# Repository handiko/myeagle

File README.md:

# myeagle
Collection of my eagle

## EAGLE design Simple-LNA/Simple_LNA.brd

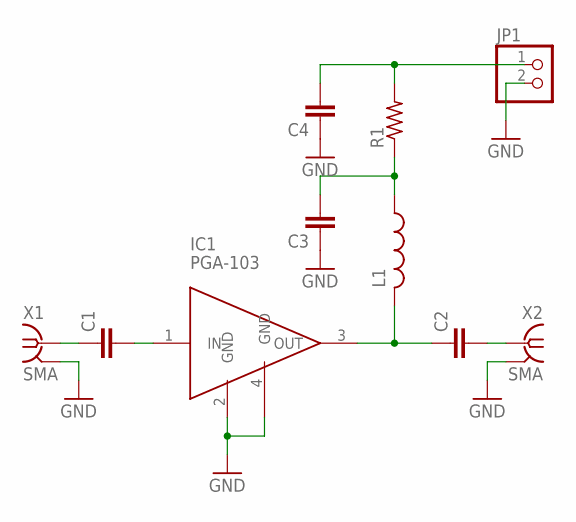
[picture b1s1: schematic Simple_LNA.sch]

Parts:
C1, C2, C3, C4: C-EUC0805; C0805
IC1: PGA-103; SOT89
JP1: PINHD-1X2; 1X02
L1: L-USL3216C; L3216C
R1: R-US_R0805; R0805
X1, X2: SMA; J502-ND-142-0701-801/806

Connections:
GND: C3.1, C4.1, IC1.2 (GND), IC1.4 (GND), JP1.2, X1.G@1 (2), X1.G@2 (2), X1.G@3 (2), X1.G@4 (2), X2.G@1 (2), X2.G@2 (2), X2.G@3 (2), X2.G@4 (2)
unnamed: C1.1, X1.1
unnamed: C1.2, IC1.1 (IN)
unnamed: C2.2, X2.1
unnamed: C2.1, IC1.3 (OUT), L1.2
unnamed: C4.2, JP1.1, R1.2
unnamed: C3.2, L1.1, R1.1

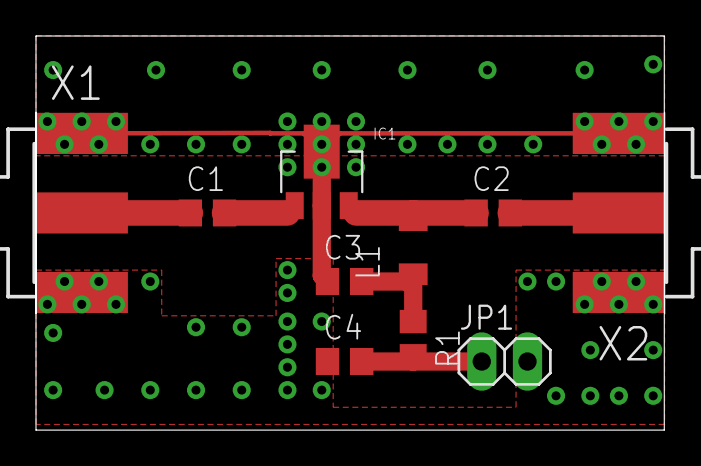
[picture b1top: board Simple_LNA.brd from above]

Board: 2 copper layers, 34.9 x 21.9 mm, 10 parts (0 on the bottom side), 7 nets.

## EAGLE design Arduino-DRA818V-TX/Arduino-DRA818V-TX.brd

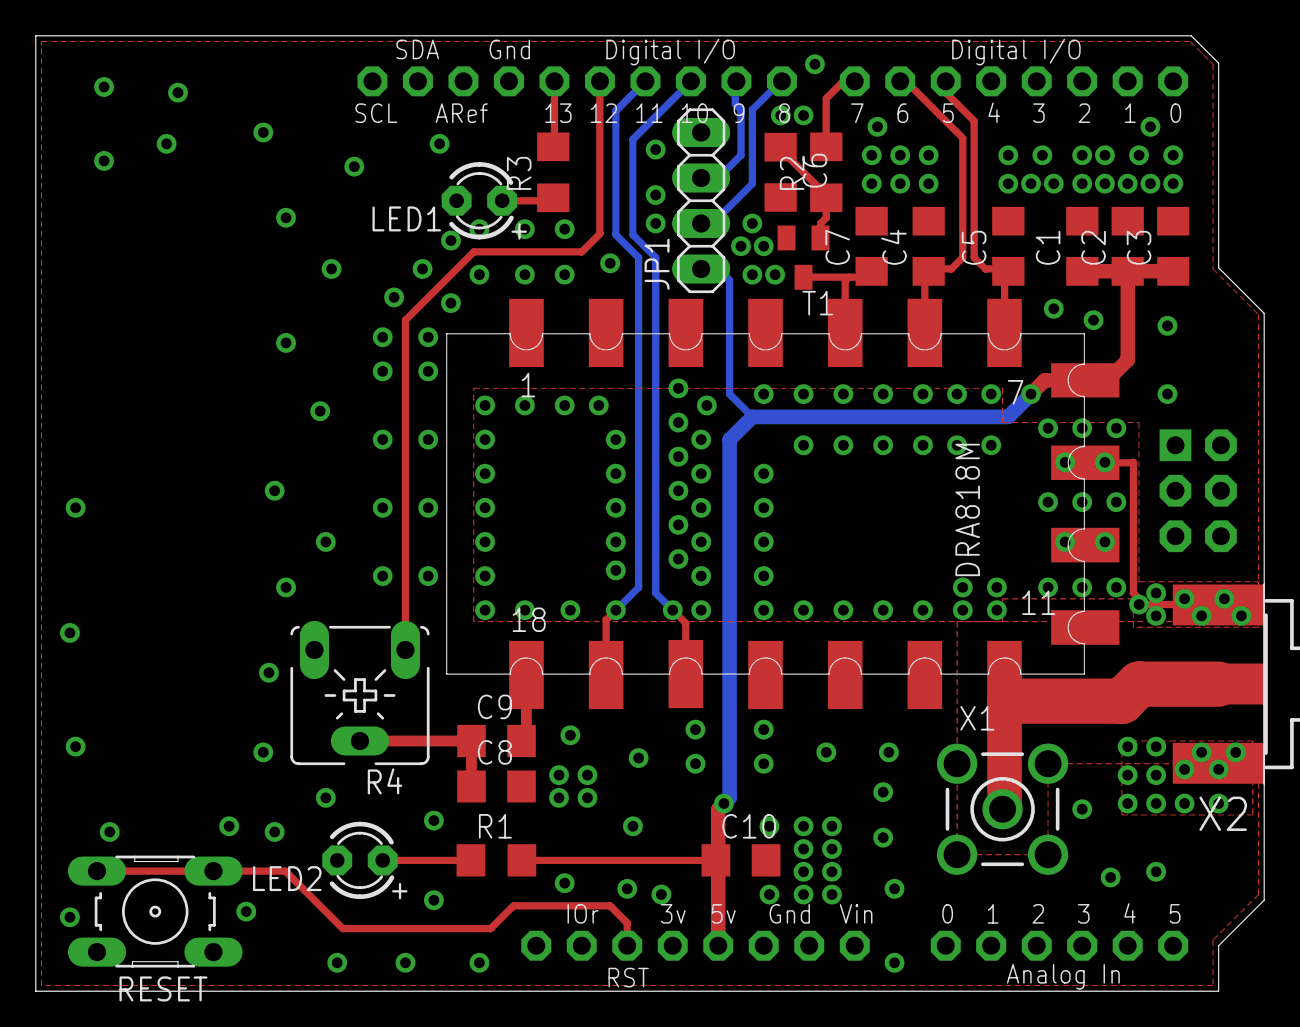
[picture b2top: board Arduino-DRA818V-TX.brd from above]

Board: 2 copper layers, 68.6 x 53.3 mm, 23 parts (0 on the bottom side), 19 nets.

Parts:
C1, C10: 1n; C1206
C2: 10n; C1206
C3, C9: 1u; C1206
C4, C5, C6, C7, C8: 100n; C1206
DRA818V: DRA818A
JP1: 1X04
LED1, LED2: LED3MM
M1: ARDUINO_R3_ICSP; ARDUINOR3_ICSP
R1, R3: 560; R1206
R2: 1k; R1206
R4: 10k; CA6V
RESET: Reset; B3F-10XX
T1: SOT23-BEC
X1: SMA; LTI-SASF54GT
X2: SMA; J502-ND-142-0701-801/806

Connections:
+5V: C1.1, C2.1, C3.1, C10.1, DRA818V.8, JP1.1, M1.5V, R1.2
AF_NORM: C9.2, DRA818V.18
AF_OUT: M1.D12, R4.A
GND: C1.2, C2.2, C3.2, C4.2, C5.2, C6.2, C7.2, C8.2, C10.2, DRA818V.9, DRA818V.10, JP1.4, LED1.K, LED2.K, M1.GND, M1.GND@1, M1.GND@2, M1.GND@3, R4.E, RESET.1, RESET.2, T1.E, X1.2, X1.3, X1.4, X1.5, X2.G@1, X2.G@2, X2.G@3, X2.G@4
LED_BUILTIN: M1.D13, R3.2
unnamed: DRA818V.12, X1.1, X2.1
unnamed: C6.1, R2.1, T1.B
unnamed: LED1.A, R3.1
unnamed: C8.1, C9.1, R4.S
unnamed: LED2.A, R1.1
PD: C4.1, DRA818V.6, M1.D6
POW: C5.1, DRA818V.7, M1.D5
PTT: M1.D7, R2.2
PTT_SW: C7.1, DRA818V.5, T1.C
RESET: M1.RESET, RESET.3, RESET.4
RXD_DRJ: DRA818V.16, M1.D10
RXD_GPS: JP1.2, M1.D8
TXD_DRJ: DRA818V.17, M1.D11
TXD_GPS: JP1.3, M1.D9

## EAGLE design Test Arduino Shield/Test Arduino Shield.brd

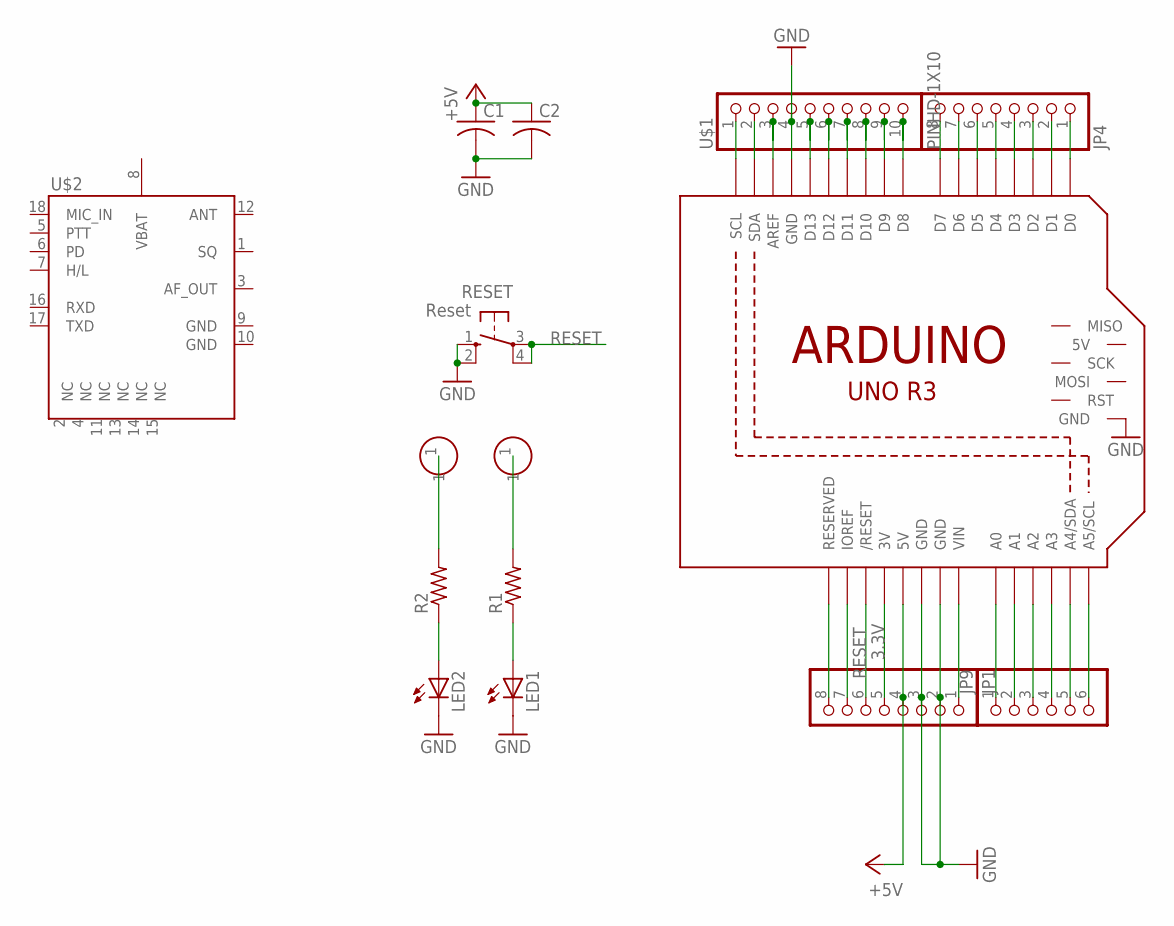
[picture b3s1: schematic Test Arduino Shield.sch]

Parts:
C1, C2: C-US025-025X050; C025-025X050
JP1, JP4: PINHD-1X8BIG; 1X08-BIG
JP9: PINHD-1X6B; 1X06-BIG
LED1, LED2: LED3MM
M1: ARDUINO_R3_ICSP; ARDUINOR3_ICSP
R1, R2: R-US_0207/5V; 0207/5V
RESET: Reset; B3F-10XX
U$1: PINHD-1X10; 1X10-BIG
U$2: DRA818A
U$4, U$7: PERFHOLE

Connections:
3.3V: JP1.5, M1.3V
+5V: C1.1, C2.1, JP1.4, M1.5V
GND: C1.2, C2.2, JP1.2, JP1.3, LED1.K (C), LED2.K (C), M1.GND, M1.GND@1 (GND), M1.GND@2 (GND), M1.GND@3 (GND), RESET.1 (S), RESET.2 (S1), U$1.4
unnamed: M1.AREF, U$1.3
unnamed: JP1.8, M1.RESERVED
unnamed: M1.D13, U$1.5
unnamed: LED1.A, R1.1
unnamed: JP1.7, M1.IOREF
unnamed: R1.2, U$7.1
unnamed: R2.2, U$4.1
unnamed: LED2.A, R2.1
unnamed: M1.D12, U$1.6
unnamed: M1.D11, U$1.7
unnamed: M1.D10, U$1.8
unnamed: M1.D9, U$1.9
unnamed: M1.D8, U$1.10
unnamed: JP9.1, M1.A0
unnamed: JP9.2, M1.A1
unnamed: JP9.3, M1.A2
unnamed: JP9.4, M1.A3
unnamed: JP9.5, M1.A4 (A4/SDA)
unnamed: JP9.6, M1.A5 (A5/SCL)
unnamed: JP4.1, M1.D0
unnamed: JP4.2, M1.D1
unnamed: JP4.3, M1.D2
unnamed: JP4.4, M1.D3
unnamed: JP4.5, M1.D4
unnamed: JP4.6, M1.D5
unnamed: JP4.7, M1.D6
unnamed: JP4.8, M1.D7
unnamed: JP1.1, M1.VIN
unnamed: M1.SCL, U$1.1
unnamed: M1.SDA, U$1.2
RESET: JP1.6, M1.RESET (/RESET), RESET.3, RESET.4 (P1)

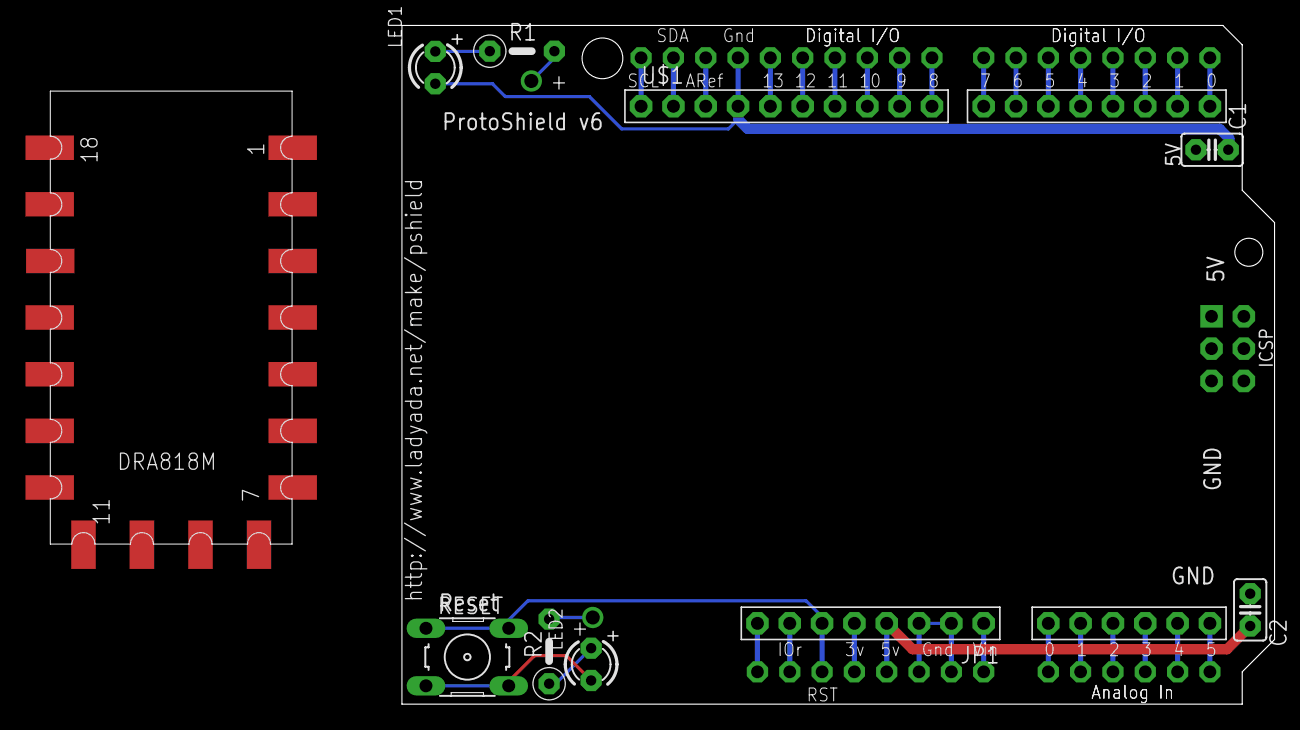
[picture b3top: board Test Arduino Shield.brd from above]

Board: 2 copper layers, 68.6 x 53.3 mm, 16 parts (1 on the bottom side), 34 nets.

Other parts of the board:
U$36: ADAFRUIT_9MM

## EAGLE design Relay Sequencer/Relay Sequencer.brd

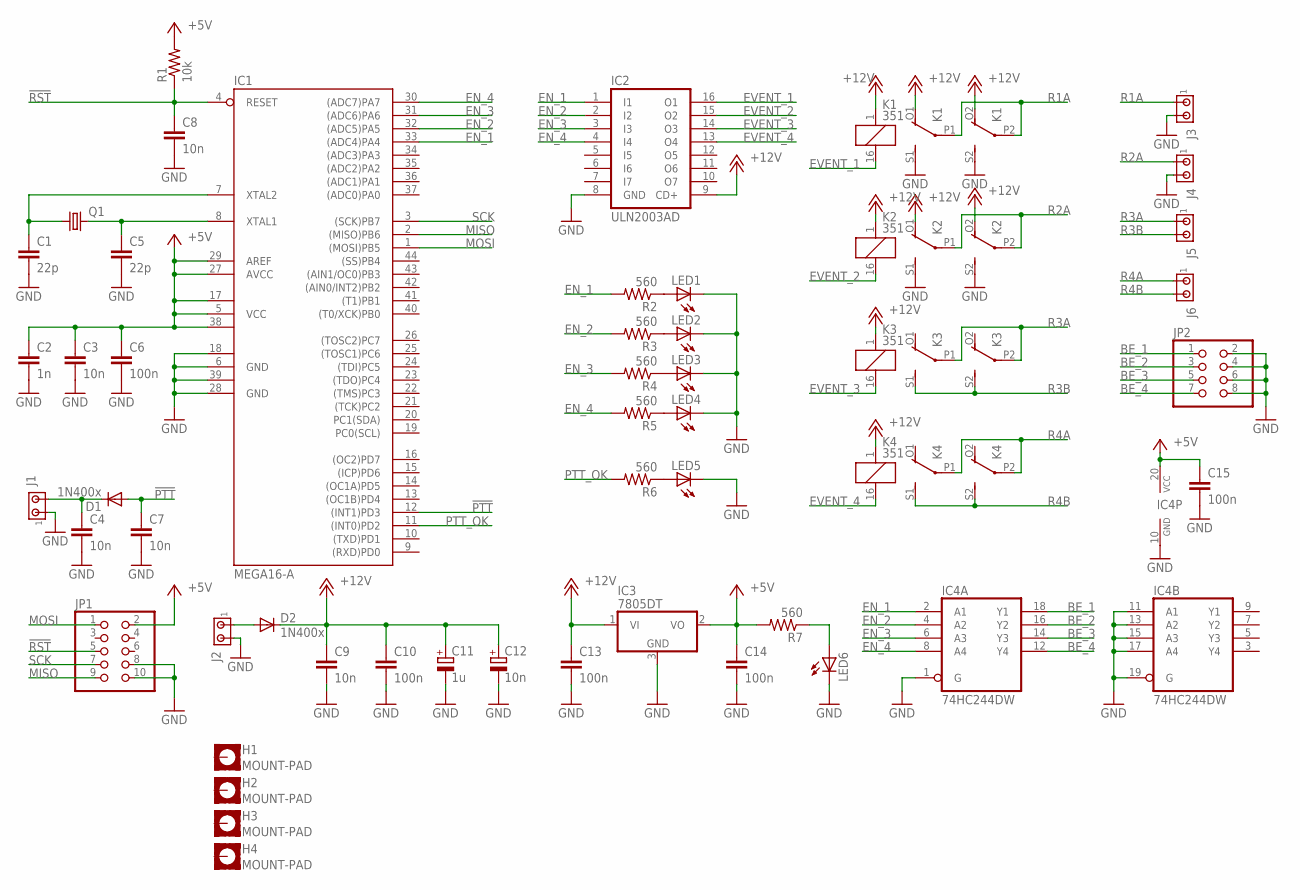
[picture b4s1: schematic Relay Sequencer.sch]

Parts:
C1, C5: 22p; C1206
C2: 1n; C1206
C3, C4, C7, C8, C9: 10n; C1206
C6, C10, C13, C14, C15: 100n; C1206
C11: 1u; E5-8,5
C12: 10n; E5-13
D1, D2: 1N400x; DO35-10
H1, H2, H3, H4: MOUNT-PAD; 2,8-PAD-SQUARE
IC1: MEGA16-A; TQFP44
IC2: ULN2003AD; SO16
IC3: 7805DT; TO252
IC4: 74HC244DW; SO20W
J1, J2, J3, J4, J5, J6: MTA02-156; 1X2MTA
JP1: PINHD-2X5; 2X05
JP2: PINHD-2X4; 2X04
K1, K2, K3, K4: 351
LED1, LED2, LED3, LED4, LED5, LED6: LED3MM
Q1: CRYSTALHC49S; HC49/S
R1: 10k; M1206
R2, R3, R4, R5, R6, R7: 560; M1206

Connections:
!PTT: C7.1, D1.A, IC1.12 ((INT1)PD3)
!RST: C8.1, IC1.4 (RESET), JP1.5, R1.1
+5V: C2.1, C3.1, C6.1, C14.1, C15.1, IC1.5 (VCC), IC1.17 (VCC1), IC1.27 (AVCC), IC1.29 (AREF), IC1.38 (VCC2), IC3.2 (VO), IC4.20 (VCC), JP1.2, R1.2, R7.2
+12V: C9.1, C10.1, C11.+, C12.+, C13.1, D2.C, IC2.9 (CD+), IC3.1 (VI), K1.1, K1.O1 (O), K1.O2 (O), K2.1, K2.O1 (O), K2.O2 (O), K3.1, K4.1
BE_1: IC4.18 (Y1), JP2.1
BE_2: IC4.16 (Y2), JP2.3
BE_3: IC4.14 (Y3), JP2.5
BE_4: IC4.12 (Y4), JP2.7
EN_1: IC1.33 ((ADC4)PA4), IC2.1 (I1), IC4.2 (A1), R2.2
EN_2: IC1.32 ((ADC5)PA5), IC2.2 (I2), IC4.4 (A2), R3.2
EN_3: IC1.31 ((ADC6)PA6), IC2.3 (I3), IC4.6 (A3), R4.2
EN_4: IC1.30 ((ADC7)PA7), IC2.4 (I4), IC4.8 (A4), R5.2
EVENT_1: IC2.16 (O1), K1.16 (2)
EVENT_2: IC2.15 (O2), K2.16 (2)
EVENT_3: IC2.14 (O3), K3.16 (2)
EVENT_4: IC2.13 (O4), K4.16 (2)
GND: C1.2, C2.2, C3.2, C4.2, C5.2, C6.2, C7.2, C8.2, C9.2, C10.2, C11.-, C12.-, C13.2, C14.2, C15.2, IC1.6 (GND), IC1.18 (GND1), IC1.28 (GND), IC1.39 (GND2), IC2.8 (GND), IC3.3 (GND), IC4.1 (G), IC4.10 (GND), IC4.11 (A1), IC4.13 (A2), IC4.15 (A3), IC4.17 (A4), IC4.19 (G), J1.1, J2.2, J3.2, J4.2, JP1.8, JP1.10, JP2.2, JP2.4, JP2.6, JP2.8, K1.S1 (S), K1.S2 (S), K2.S1 (S), K2.S2 (S), LED1.K (C), LED2.K (C), LED3.K (C), LED4.K (C), LED5.K (C), LED6.K (C)
MISO: IC1.2 ((MISO)PB6), JP1.9
MOSI: IC1.1 ((MOSI)PB5), JP1.1
unnamed: C5.1, IC1.8 (XTAL1), Q1.2
unnamed: C1.1, IC1.7 (XTAL2), Q1.1
unnamed: LED3.A, R4.1
unnamed: LED4.A, R5.1
unnamed: LED1.A, R2.1
unnamed: LED2.A, R3.1
unnamed: LED5.A, R6.1
unnamed: C4.1, D1.C, J1.2
unnamed: D2.A, J2.1
unnamed: LED6.A, R7.1
PTT_OK: IC1.11 ((INT0)PD2), R6.2
R1A: J3.1, K1.P1, K1.P2
R2A: J4.1, K2.P1, K2.P2
R3A: J5.1, K3.P1, K3.P2
R3B: J5.2, K3.S1 (S), K3.S2 (S)
R4A: J6.1, K4.P1, K4.P2
R4B: J6.2, K4.S1 (S), K4.S2 (S)
SCK: IC1.3 ((SCK)PB7), JP1.7

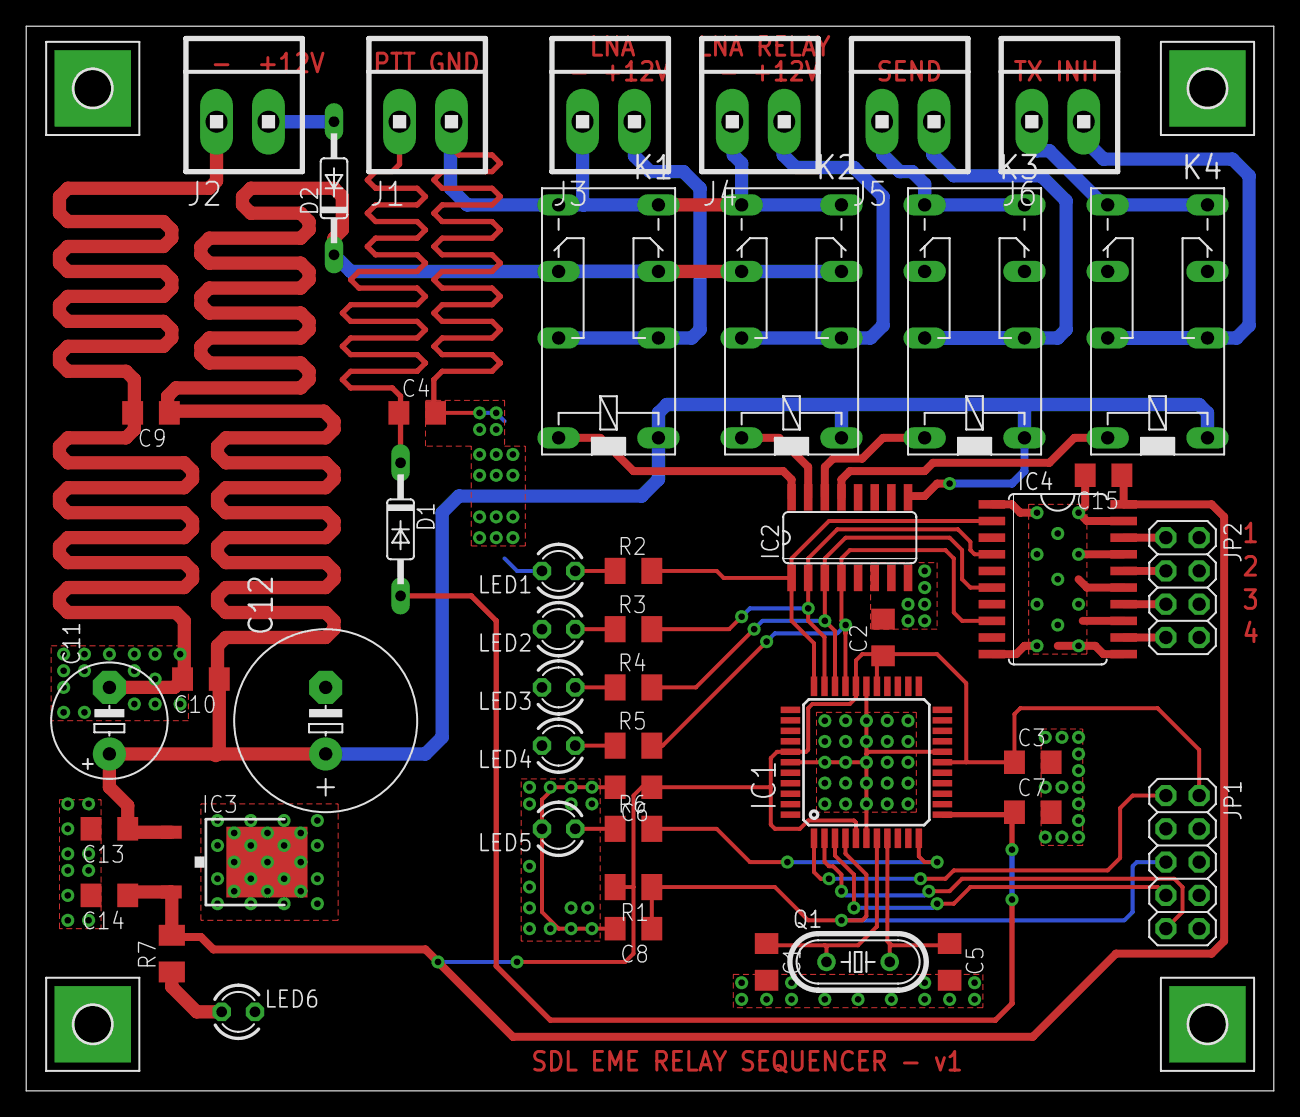
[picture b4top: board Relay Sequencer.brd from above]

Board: 2 copper layers, 95.2 x 81.3 mm, 51 parts (0 on the bottom side), 37 nets.

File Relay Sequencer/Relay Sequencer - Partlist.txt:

Partlist

Exported from Relay Sequencer.sch at 11/7/2018 9:09 PM

EAGLE Version 7.7.0 Copyright (c) 1988-2016 CadSoft

Assembly variant: 

Part     Value          Device              Package        Library  Sheet

C1       22p            C-EUC1206           C1206          rcl      1
C2       1n             C-EUC1206           C1206          rcl      1
C3       10n            C-EUC1206           C1206          rcl      1
C4       10n            C-EUC1206           C1206          rcl      1
C5       22p            C-EUC1206           C1206          rcl      1
C6       100n           C-EUC1206           C1206          rcl      1
C7       10n            C-EUC1206           C1206          rcl      1
C8       10n            C-EUC1206           C1206          rcl      1
C9       10n            C-EUC1206           C1206          rcl      1
C10      100n           C-EUC1206           C1206          rcl      1
C11      1u             CPOL-EUE5-8.5       E5-8,5         rcl      1
C12      10n            CPOL-EUE5-13        E5-13          rcl      1
C13      100n           C-EUC1206           C1206          rcl      1
C14      100n           C-EUC1206           C1206          rcl      1
C15      100n           C-EUC1206           C1206          rcl      1
D1       1N400x         1N4148DO35-10       DO35-10        diode    1
D2       1N400x         1N4148DO35-10       DO35-10        diode    1
H1       MOUNT-PAD      MOUNT-PAD-SQUARE2.8 2,8-PAD-SQUARE holes    1
H2       MOUNT-PAD      MOUNT-PAD-SQUARE2.8 2,8-PAD-SQUARE holes    1
H3       MOUNT-PAD      MOUNT-PAD-SQUARE2.8 2,8-PAD-SQUARE holes    1
H4       MOUNT-PAD      MOUNT-PAD-SQUARE2.8 2,8-PAD-SQUARE holes    1
IC1      MEGA16-A       MEGA16-A            TQFP44         atmel    1
IC2      ULN2003AD      ULN2003AD           SO16           uln-udn  1
IC3      7805DT         7805DT              TO252          linear   1
IC4      74HC244DW      74HC244DW           SO20W          74xx-eu  1
J1                      MTA02-156           1X2MTA         con-amp  1
J2                      MTA02-156           1X2MTA         con-amp  1
J3                      MTA02-156           1X2MTA         con-amp  1
J4                      MTA02-156           1X2MTA         con-amp  1
J5                      MTA02-156           1X2MTA         con-amp  1
J6                      MTA02-156           1X2MTA         con-amp  1
JP1                     PINHD-2X5           2X05           pinhead  1
JP2                     PINHD-2X4           2X04           pinhead  1
K1       351            351                 351            relay    1
K2       351            351                 351            relay    1
K3       351            351                 351            relay    1
K4       351            351                 351            relay    1
LED1                    LED3MM              LED3MM         led      1
LED2                    LED3MM              LED3MM         led      1
LED3                    LED3MM              LED3MM         led      1
LED4                    LED3MM              LED3MM         led      1
LED5                    LED3MM              LED3MM         led      1
LED6                    LED3MM              LED3MM         led      1
Q1                      CRYSTALHC49S        HC49/S         crystal  1
R1       10k            R-US_M1206          M1206          rcl      1
R2       560            R-US_M1206          M1206          rcl      1
R3       560            R-US_M1206          M1206          rcl      1
R4       560            R-US_M1206          M1206          rcl      1
R5       560            R-US_M1206          M1206          rcl      1
R6       560            R-US_M1206          M1206          rcl      1
R7       560            R-US_M1206          M1206          rcl      1

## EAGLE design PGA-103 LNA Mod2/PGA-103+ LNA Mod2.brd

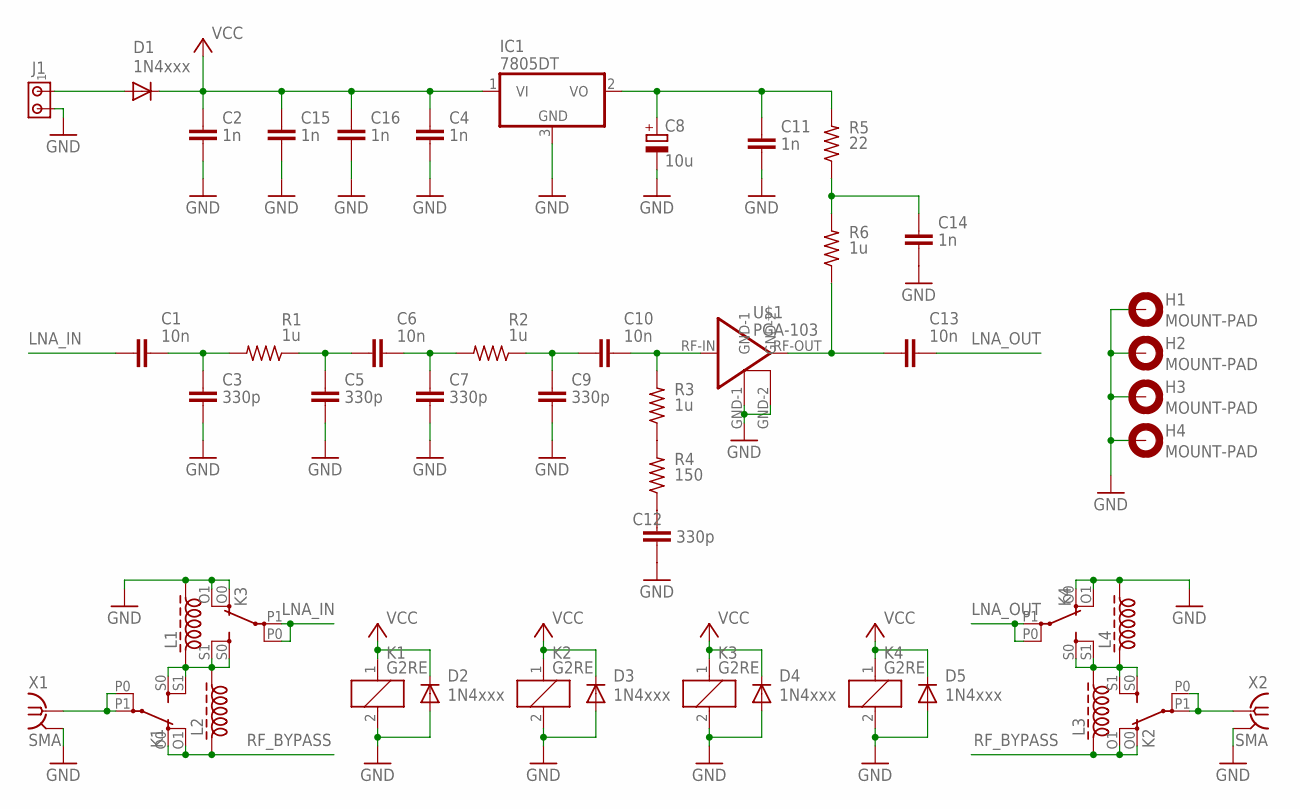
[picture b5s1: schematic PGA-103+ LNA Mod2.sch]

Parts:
C1, C6, C10, C13: 10n; C1206
C2, C4, C11, C14, C15, C16: 1n; C1206
C3, C5, C7, C9, C12: 330p; C1206
C8: 10u; B/3528-21R
D1, D2, D3, D4, D5: 1N4xxx; DO35-7
H1, H2, H3, H4: MOUNT-PAD; 2,8-PAD
IC1: 7805DT; TO252
J1: MTA02-156; 1X2MTA
K1, K2, K3, K4: G2RE
L1, L2, L3, L4: Z28/70CW; Z28/7
R1, R2, R3, R6: 1u; M1206
R4: 150; M1206
R5: 22; M1206
U$1: PGA-103; DF782
X1, X2: SMA; J502-ND-142-0701-851/861

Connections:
ANT: K1.P0, K1.P1, X1.1
GND: C2.2, C3.1, C4.2, C5.1, C7.1, C8.-, C9.1, C11.2, C12.1, C14.1, C15.2, C16.2, D2.A, D3.A, D4.A, D5.A, H1.B2,8, H2.B2,8, H3.B2,8, H4.B2,8, IC1.3 (GND), J1.2, K1.2, K2.2, K3.2, K3.O0 (O), K3.O1 (O), K4.2, K4.O0 (O), K4.O1 (O), L1.2, L4.2, U$1.GND-1, U$1.GND-2, X1.G@1 (2), X1.G@2 (2), X1.G@3 (2), X1.G@4 (2), X2.G@1 (2), X2.G@2 (2), X2.G@3 (2), X2.G@4 (2)
LNA_IN: C1.1, K3.P0, K3.P1
LNA_OUT: C13.2, K4.P0, K4.P1
unnamed: C10.2, R3.2, U$1.RF-IN
unnamed: C13.1, R6.1, U$1.RF-OUT
unnamed: C8.+, C11.1, IC1.2 (VO), R5.2
unnamed: D1.A, J1.1
unnamed: C9.2, C10.1, R2.1
unnamed: C14.2, R5.1, R6.2
unnamed: R3.1, R4.2
unnamed: C12.2, R4.1
unnamed: C6.2, C7.2, R2.2
unnamed: C5.2, C6.1, R1.1
unnamed: C1.2, C3.2, R1.2
unnamed: K1.S0 (S), K1.S1 (S), K3.S0 (S), K3.S1 (S), L1.1, L2.2
unnamed: K2.S0 (S), K2.S1 (S), K4.S0 (S), K4.S1 (S), L3.2, L4.1
RF_BYPASS: K1.O0 (O), K1.O1 (O), K2.O0 (O), K2.O1 (O), L2.1, L3.1
TRX: K2.P0, K2.P1, X2.1
VCC: C2.1, C4.1, C15.1, C16.1, D1.C, D2.C, D3.C, D4.C, D5.C, IC1.1 (VI), K1.1, K2.1, K3.1, K4.1

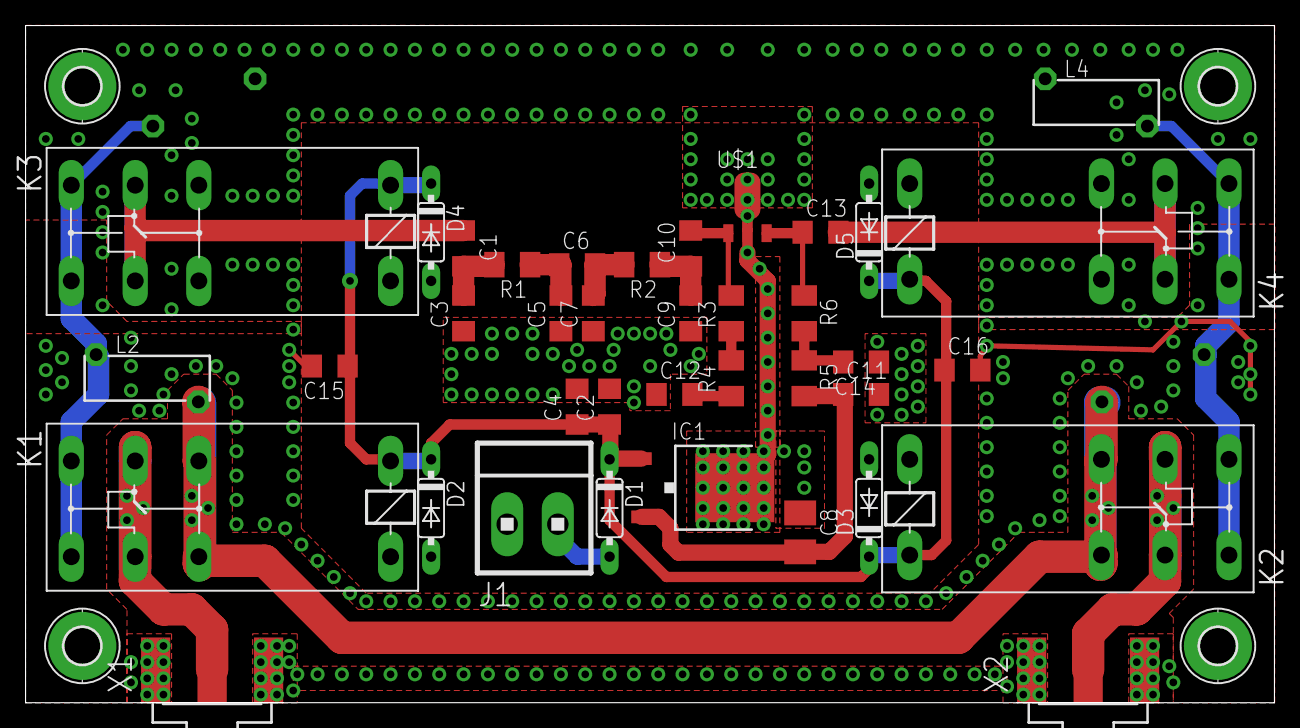
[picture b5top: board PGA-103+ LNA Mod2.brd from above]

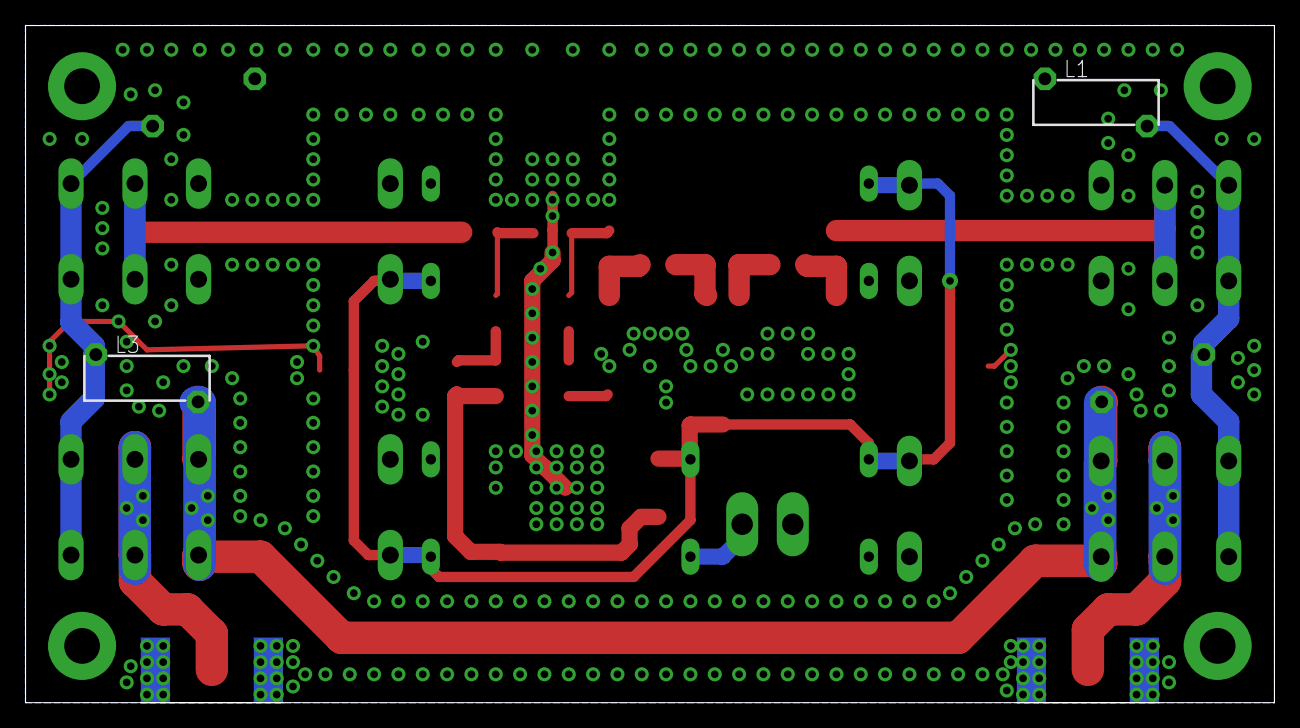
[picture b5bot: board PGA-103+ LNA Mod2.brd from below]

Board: 2 copper layers, 97.8 x 53.0 mm, 44 parts (2 on the bottom side), 20 nets.

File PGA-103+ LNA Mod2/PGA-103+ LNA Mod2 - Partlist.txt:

Partlist

Exported from PGA-103+ LNA Mod2.sch at 11/7/2018 6:19 AM

EAGLE Version 7.7.0 Copyright (c) 1988-2016 CadSoft

Assembly variant: 

Part     Value          Device               Package                  Library         Sheet

C1       10n            C-EUC1206            C1206                    rcl             1
C2       1n             C-EUC1206            C1206                    rcl             1
C3       330p           C-EUC1206            C1206                    rcl             1
C4       1n             C-EUC1206            C1206                    rcl             1
C5       330p           C-EUC1206            C1206                    rcl             1
C6       10n            C-EUC1206            C1206                    rcl             1
C7       330p           C-EUC1206            C1206                    rcl             1
C8       10u            CPOL-EUB/3528-21R    B/3528-21R               rcl             1
C9       330p           C-EUC1206            C1206                    rcl             1
C10      10n            C-EUC1206            C1206                    rcl             1
C11      1n             C-EUC1206            C1206                    rcl             1
C12      330p           C-EUC1206            C1206                    rcl             1
C13      10n            C-EUC1206            C1206                    rcl             1
C14      1n             C-EUC1206            C1206                    rcl             1
C15      1n             C-EUC1206            C1206                    rcl             1
C16      1n             C-EUC1206            C1206                    rcl             1
D1       1N4xxx         1N4148DO35-7         DO35-7                   diode           1
D2       1N4xxx         1N4148DO35-7         DO35-7                   diode           1
D3       1N4xxx         1N4148DO35-7         DO35-7                   diode           1
D4       1N4xxx         1N4148DO35-7         DO35-7                   diode           1
D5       1N4xxx         1N4148DO35-7         DO35-7                   diode           1
H1       MOUNT-PAD      MOUNT-PAD-ROUND2.8   2,8-PAD                  holes           1
H2       MOUNT-PAD      MOUNT-PAD-ROUND2.8   2,8-PAD                  holes           1
H3       MOUNT-PAD      MOUNT-PAD-ROUND2.8   2,8-PAD                  holes           1
H4       MOUNT-PAD      MOUNT-PAD-ROUND2.8   2,8-PAD                  holes           1
IC1      7805DT         7805DT               TO252                    linear          1
J1                      MTA02-156            1X2MTA                   con-amp         1
K1       G2RE           G2RE                 G2RE                     relay           1
K2       G2RE           G2RE                 G2RE                     relay           1
K3       G2RE           G2RE                 G2RE                     relay           1
K4       G2RE           G2RE                 G2RE                     relay           1
L1                      Z28/70CW             Z28/7                    inductor-neosid 1
L2                      Z28/70CW             Z28/7                    inductor-neosid 1
L3                      Z28/70CW             Z28/7                    inductor-neosid 1
L4                      Z28/70CW             Z28/7                    inductor-neosid 1
R1       1u             R-US_M1206           M1206                    rcl             1
R2       1u             R-US_M1206           M1206                    rcl             1
R3       1u             R-US_M1206           M1206                    rcl             1
R4       150            R-US_M1206           M1206                    rcl             1
R5       22             R-US_M1206           M1206                    rcl             1
R6       1u             R-US_M1206           M1206                    rcl             1
U$1      PGA-103        PGA-103              DF782                    minicircuits    1
X1       SMA            SMA-142-0701-851/861 J502-ND-142-0701-851/861 con-coax        1
X2       SMA            SMA-142-0701-851/861 J502-ND-142-0701-851/861 con-coax        1

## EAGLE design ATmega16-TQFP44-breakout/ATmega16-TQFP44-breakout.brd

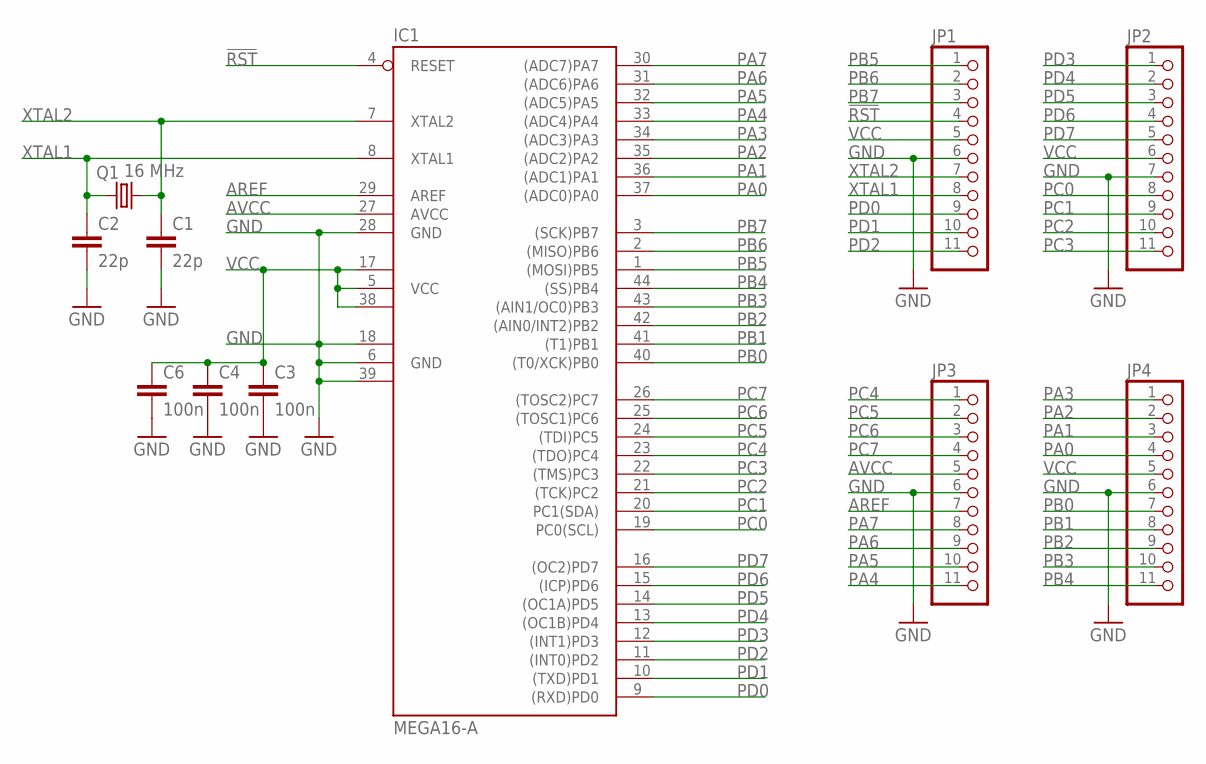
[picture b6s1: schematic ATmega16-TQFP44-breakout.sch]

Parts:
C1, C2: 22p; C1206
C3, C4, C6: 100n; C1206
IC1: MEGA16-A; TQFP44
JP1, JP2, JP3, JP4: PINHD-1X11; 1X11
Q1: 16 MHz; HC49/S

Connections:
!RST: IC1.4 (RESET), JP1.4
AREF: IC1.29 (AREF), JP3.7
AVCC: IC1.27 (AVCC), JP3.5
GND: C1.2, C2.2, C3.2, C4.2, C6.2, IC1.6 (GND), IC1.18 (GND1), IC1.28 (GND), IC1.39 (GND2), JP1.6, JP2.7, JP3.6, JP4.6
PA0: IC1.37 ((ADC0)PA0), JP4.4
PA1: IC1.36 ((ADC1)PA1), JP4.3
PA2: IC1.35 ((ADC2)PA2), JP4.2
PA3: IC1.34 ((ADC3)PA3), JP4.1
PA4: IC1.33 ((ADC4)PA4), JP3.11
PA5: IC1.32 ((ADC5)PA5), JP3.10
PA6: IC1.31 ((ADC6)PA6), JP3.9
PA7: IC1.30 ((ADC7)PA7), JP3.8
PB0: IC1.40 ((T0/XCK)PB0), JP4.7
PB1: IC1.41 ((T1)PB1), JP4.8
PB2: IC1.42 ((AIN0/INT2)PB2), JP4.9
PB3: IC1.43 ((AIN1/OC0)PB3), JP4.10
PB4: IC1.44 ((SS)PB4), JP4.11
PB5: IC1.1 ((MOSI)PB5), JP1.1
PB6: IC1.2 ((MISO)PB6), JP1.2
PB7: IC1.3 ((SCK)PB7), JP1.3
PC0: IC1.19 (PC0(SCL)), JP2.8
PC1: IC1.20 (PC1(SDA)), JP2.9
PC2: IC1.21 ((TCK)PC2), JP2.10
PC3: IC1.22 ((TMS)PC3), JP2.11
PC4: IC1.23 ((TDO)PC4), JP3.1
PC5: IC1.24 ((TDI)PC5), JP3.2
PC6: IC1.25 ((TOSC1)PC6), JP3.3
PC7: IC1.26 ((TOSC2)PC7), JP3.4
PD0: IC1.9 ((RXD)PD0), JP1.9
PD1: IC1.10 ((TXD)PD1), JP1.10
PD2: IC1.11 ((INT0)PD2), JP1.11
PD3: IC1.12 ((INT1)PD3), JP2.1
PD4: IC1.13 ((OC1B)PD4), JP2.2
PD5: IC1.14 ((OC1A)PD5), JP2.3
PD6: IC1.15 ((ICP)PD6), JP2.4
PD7: IC1.16 ((OC2)PD7), JP2.5
VCC: C3.1, C4.1, C6.1, IC1.5 (VCC), IC1.17 (VCC1), IC1.38 (VCC2), JP1.5, JP2.6, JP4.5
XTAL1: C2.1, IC1.8 (XTAL1), JP1.8, Q1.1
XTAL2: C1.1, IC1.7 (XTAL2), JP1.7, Q1.2

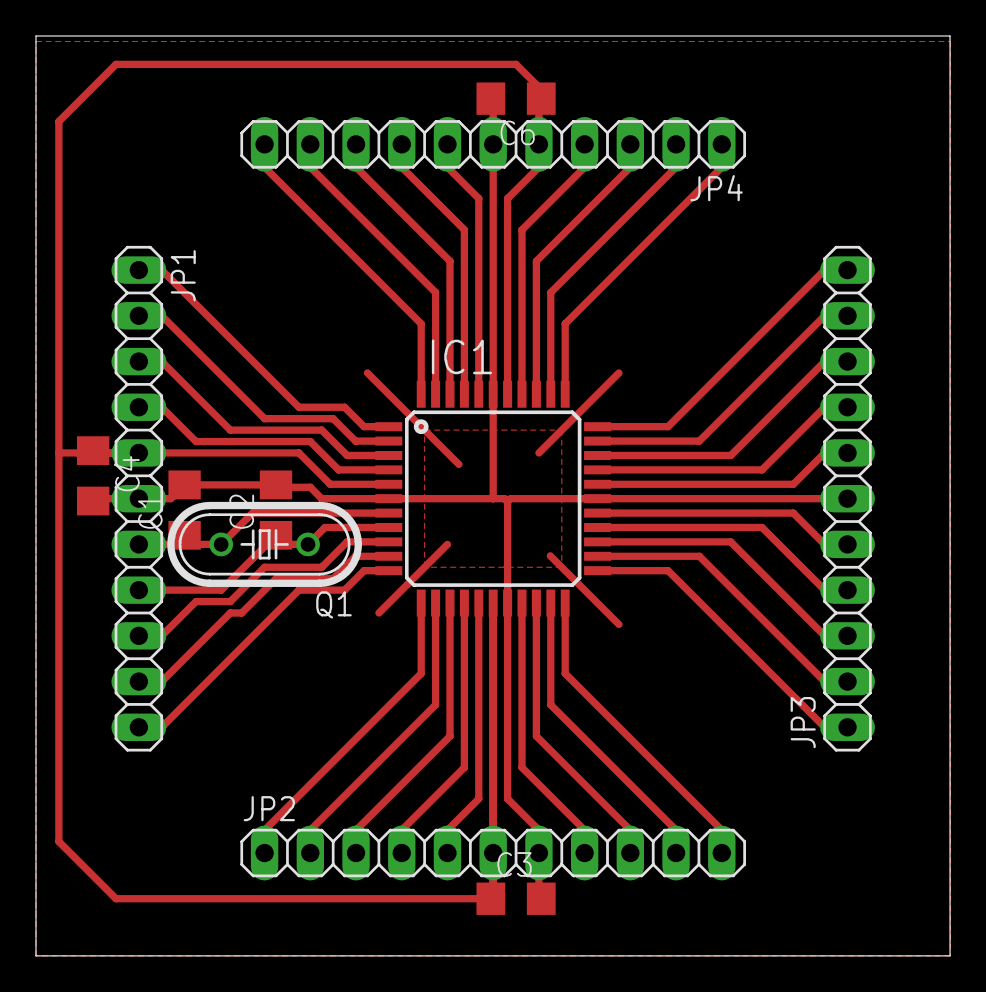
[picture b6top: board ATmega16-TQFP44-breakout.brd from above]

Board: 2 copper layers, 50.8 x 51.1 mm, 11 parts (0 on the bottom side), 39 nets.

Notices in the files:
parts and their libraries:
microbuilder: This work is placed in the public domain, and may be freely used for commercial and non-commercial work with the following conditions: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
